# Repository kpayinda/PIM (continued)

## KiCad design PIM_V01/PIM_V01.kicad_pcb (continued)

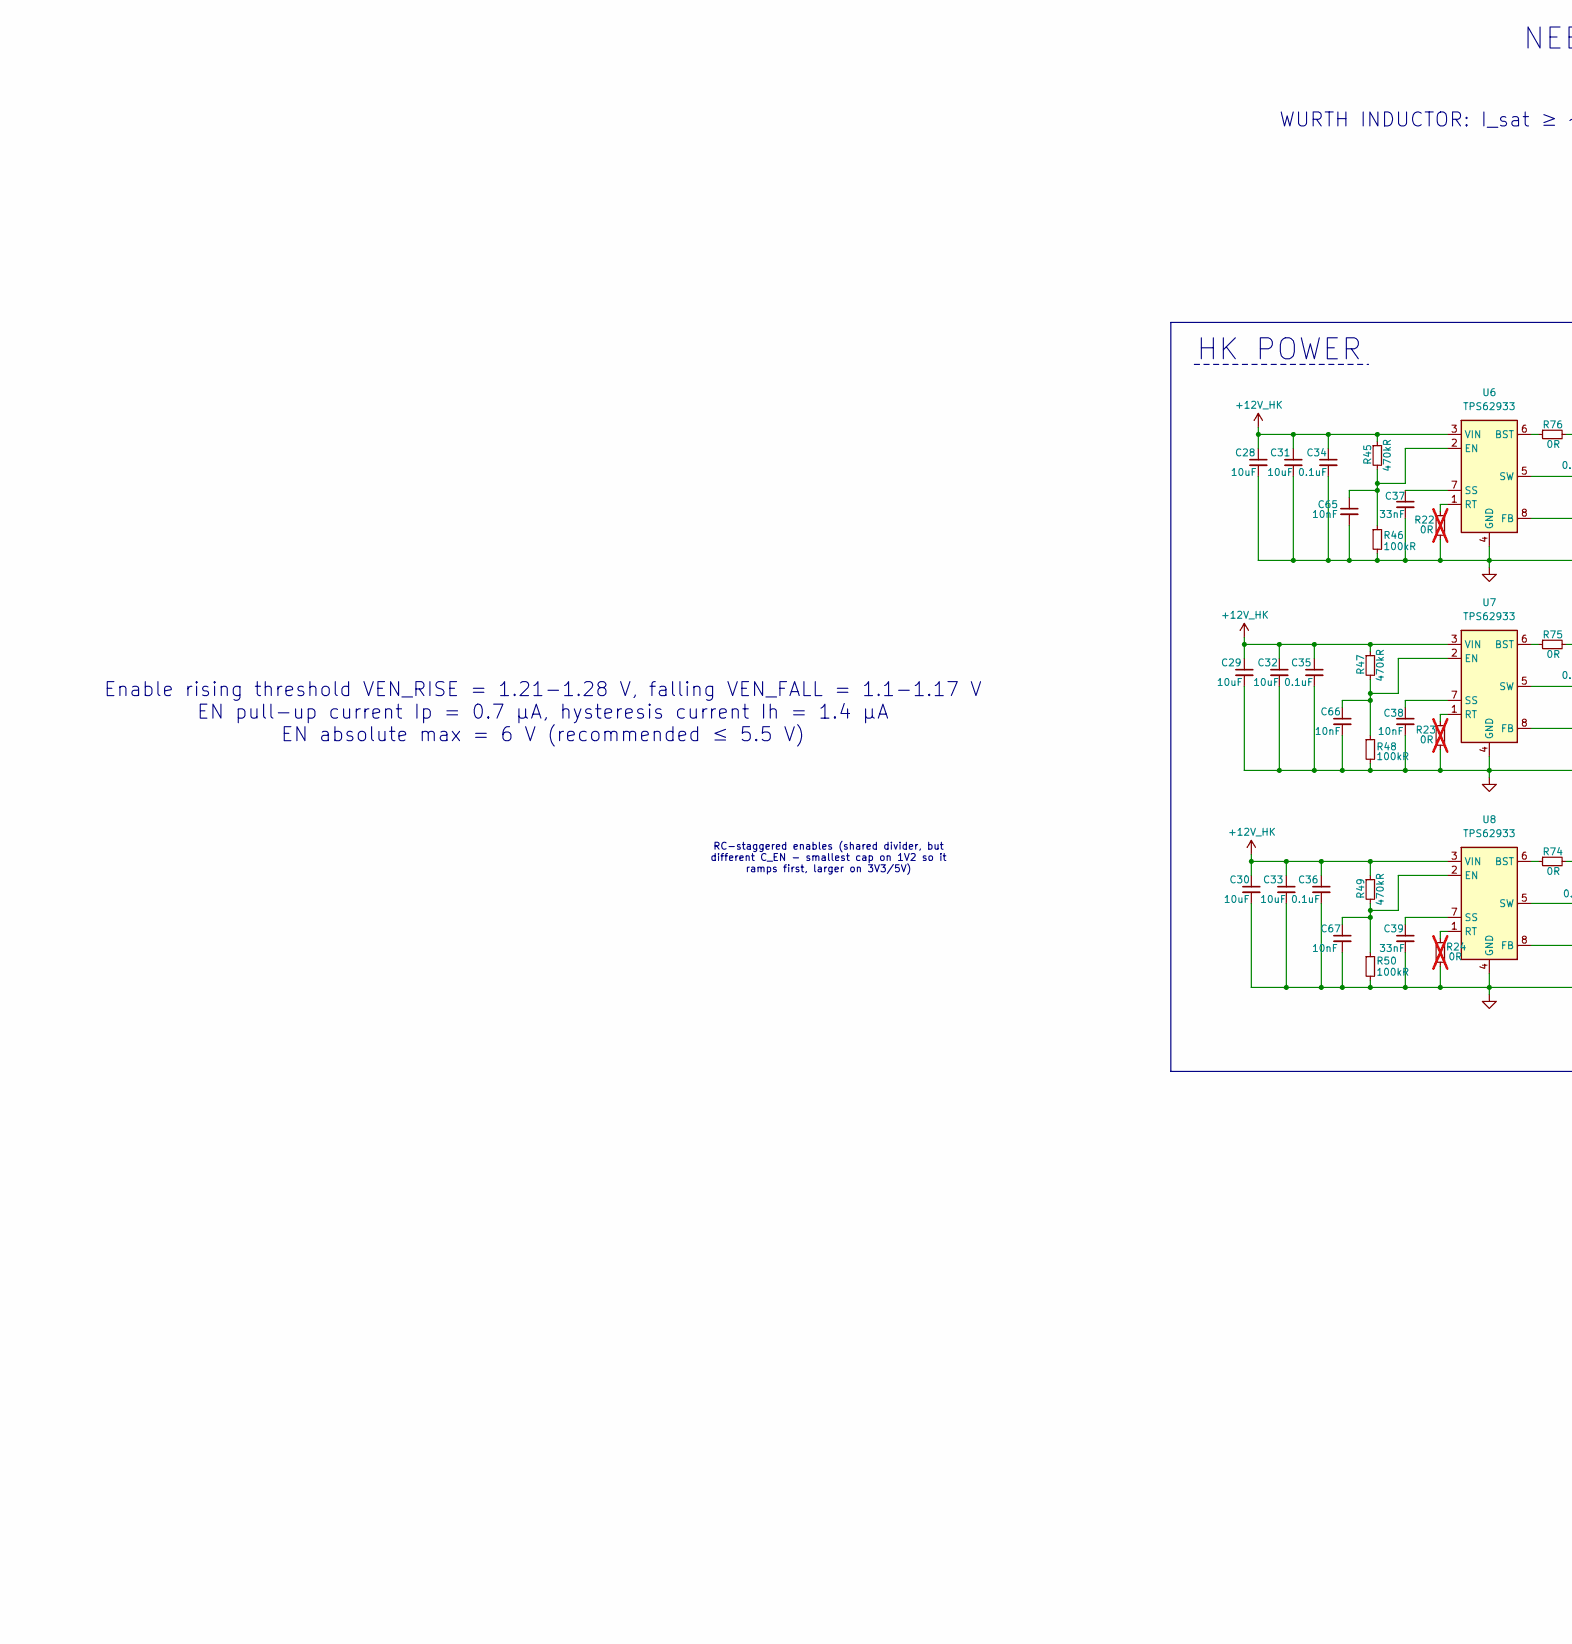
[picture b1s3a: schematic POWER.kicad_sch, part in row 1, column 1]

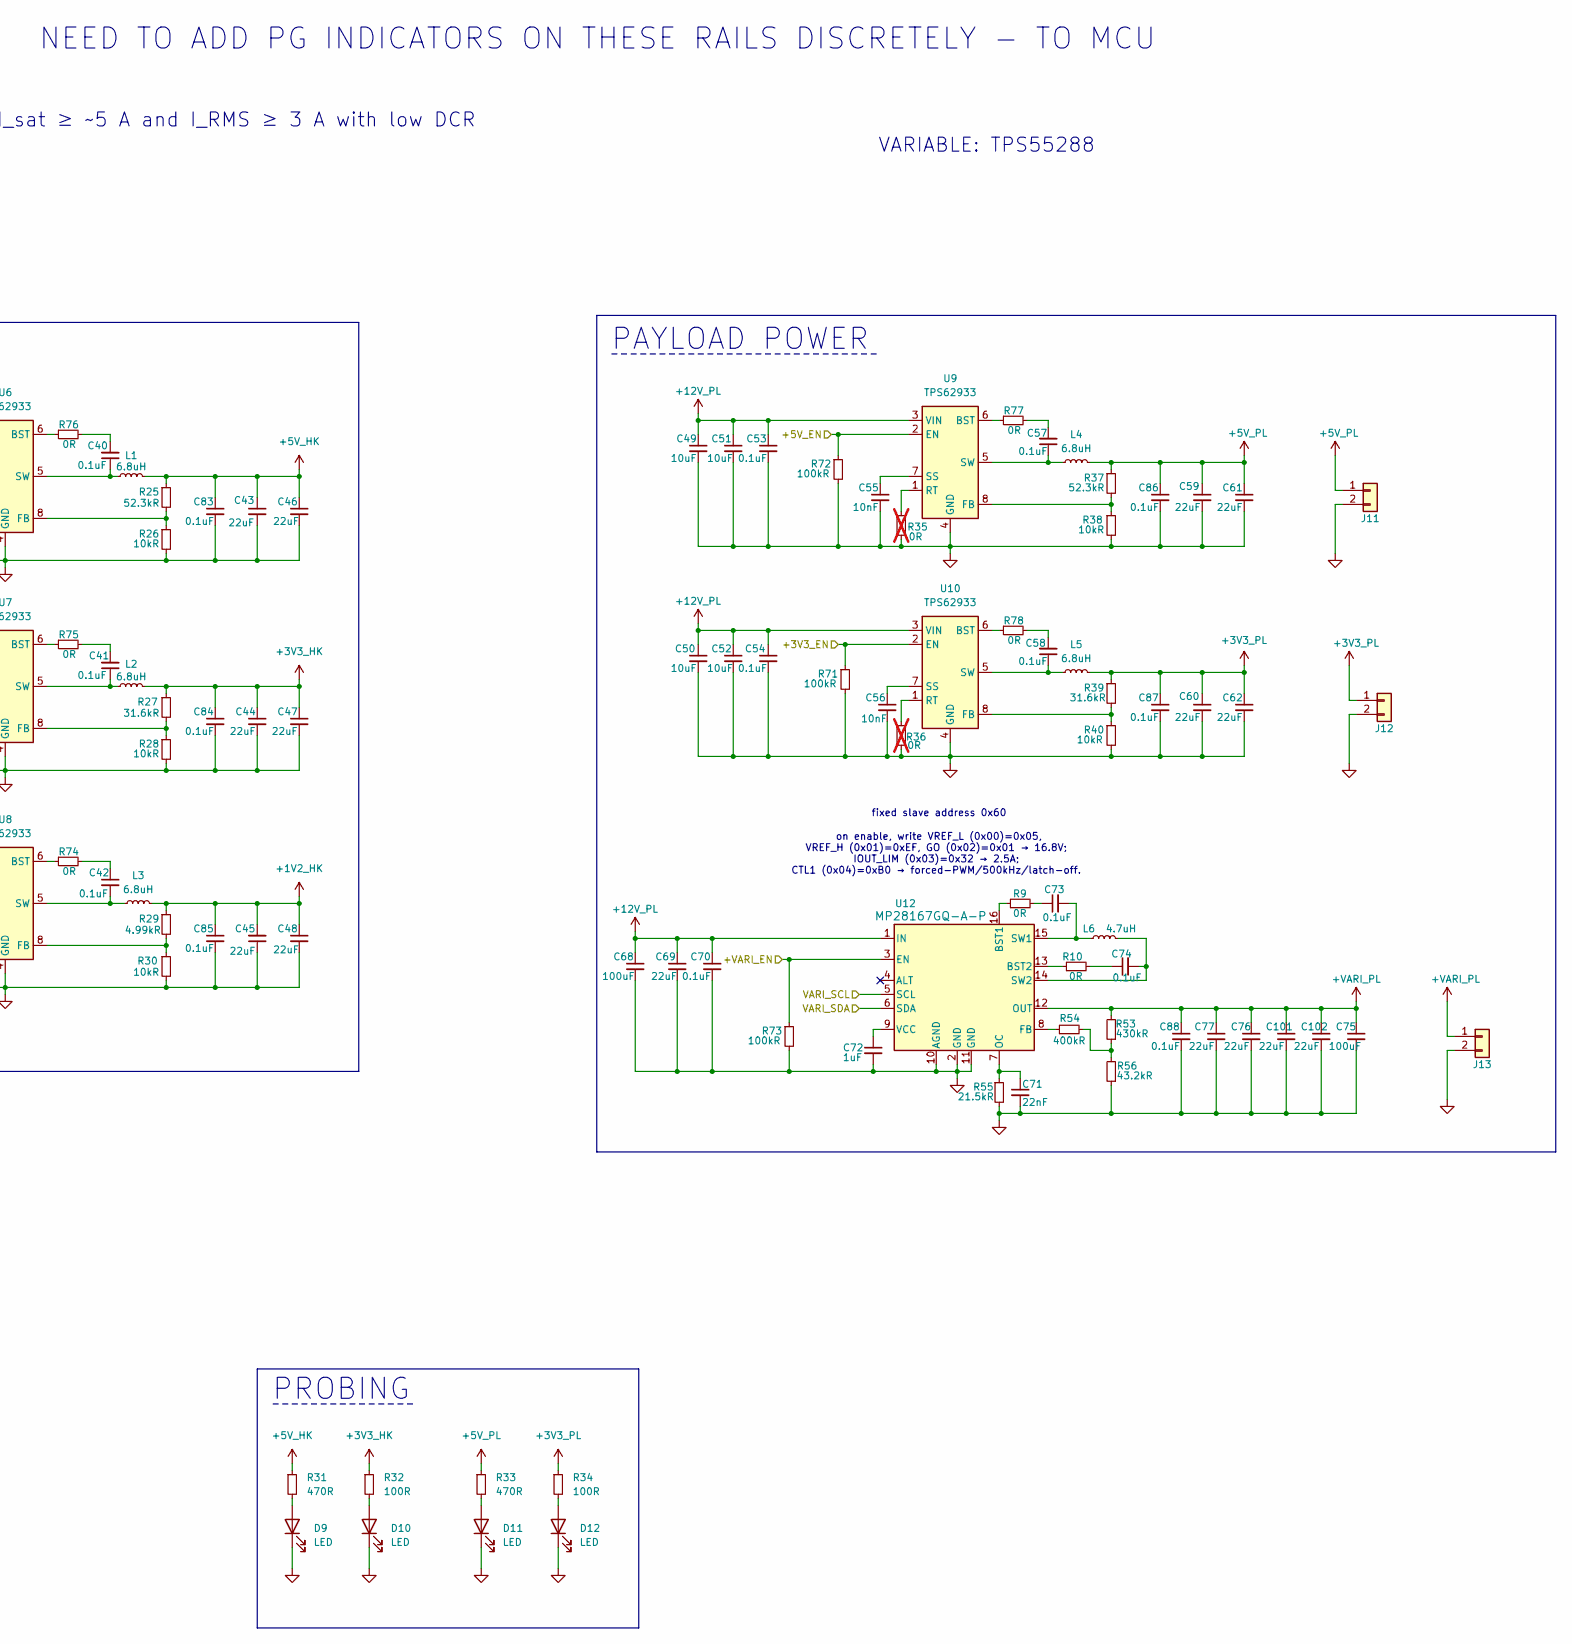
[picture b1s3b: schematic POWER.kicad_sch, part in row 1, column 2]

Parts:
C28, C29, C30, C31, C32, C33, C49, C50, C51, C52: 10uF; C_0603_1608Metric
C34, C35, C36, C40, C41, C42, C53, C54, C57, C58, C70, C73, C74, C83, C84, C85, C86, C87, C88: 0.1uF; C_0603_1608Metric
C37, C39: 33nF; C_0603_1608Metric
C38, C55, C56, C65, C66, C67: 10nF; C_0603_1608Metric
C43, C44, C45, C46, C47, C48, C59, C60, C61, C62, C69, C76, C77, C101, C102: 22uF; C_0603_1608Metric
C68, C75: 100uF; C_0603_1608Metric
C71: 22nF; C_0603_1608Metric
C72: 1uF; C_0603_1608Metric
D9, D10, D11, D12: LED; LED_0603_1608Metric; MPN XL-1608PGC-06
J11, J12, J13: Conn_01x02; PinHeader_1x02_P2.54mm_Vertical
L1, L2, L3, L4, L5: 6.8uH; L_Wurth_WE-LHMI-7030; MPN 74437346068
L6: 4.7uH; L_Wurth_WE-LHMI-7050; MPN 74437349047
R9, R10, R74, R75, R76, R77, R78: 0R; R_0603_1608Metric
R22, R23, R24, R35, R36: 0R; R_0603_1608Metric; not fitted
R25, R37: 52.3kR; R_0603_1608Metric
R26, R28, R30, R38, R40: 10kR; R_0603_1608Metric
R27, R39: 31.6kR; R_0603_1608Metric
R29: 4.99kR; R_0603_1608Metric
R31, R33: 470R; R_0603_1608Metric
R32, R34: 100R; R_0603_1608Metric
R45, R47, R49: 470kR; R_0603_1608Metric
R46, R48, R50, R71, R72, R73: 100kR; R_0603_1608Metric
R53: 430kR; R_0603_1608Metric
R54: 400kR; R_0603_1608Metric
R55: 21.5kR; R_0603_1608Metric
R56: 43.2kR; R_0603_1608Metric
U6, U7, U8, U9, U10: TPS62933; SOT-583-8
U12: MP28167GQ-A-P; QFN-16_MP28167_MNP; MPN MP28167GQ-A-P

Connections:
+1V2_HK: C45.2, C48.1, C85.1, L3.2, R29.1
+3V3_HK: C44.1, C47.1, C84.1, L2.2, R27.1, R32.1; also elsewhere on the board
+3V3_PL: C60.1, C62.1, C87.1, J12.1, L5.2, R34.1, R39.1
+5V_HK: C43.1, C46.1, C83.1, L1.2, R25.1, R31.1; also elsewhere on the board
+5V_PL: C59.1, C61.1, C86.1, J11.1, L4.2, R33.1, R37.1
+12V_HK: C28.1, C29.1, C30.1, C31.1, C32.1, C33.1, C34.1, C35.1, C36.1, R45.1, R47.1, R49.1, U6.3 (VIN), U7.3 (VIN), U8.3 (VIN); also elsewhere on the board
+12V_PL: C49.1, C50.1, C51.1, C52.1, C53.1, C54.1, C68.1, C69.1, C70.1, U9.3 (VIN), U10.3 (VIN), U12.1 (IN); also elsewhere on the board
+VARI_PL: C75.1, C76.1, C77.1, C88.1, C101.1, C102.1, J13.1, R53.2, U12.12 (OUT)
/+3V3_EN: R71.1, U10.2 (EN); also elsewhere on the board
/+5V_EN: R72.1, U9.2 (EN); also elsewhere on the board
/+VARI_EN: R73.1, U12.3 (EN); also elsewhere on the board
/VARI_SCL: U12.5 (SCL); also elsewhere on the board
/VARI_SDA: U12.6 (SDA); also elsewhere on the board
GND: C28.2, C29.2, C30.2, C31.2, C32.2, C33.2, C34.2, C35.2, C36.2, C37.2, C38.2, C39.2, C43.2, C44.2, C45.1, C46.2, C47.2, C48.2, C49.2, C50.2, C51.2, C52.2, C53.2, C54.2, C55.2, C56.2, C59.2, C60.2, C61.2, C62.2, C65.2, C66.2, C67.2, C68.2, C69.2, C70.2, C71.2, C72.2, C75.2, C76.2, C77.2, C83.2, C84.2, C85.2, C86.2, C87.2, C88.2, C101.2, C102.2, D9.1 (K), D10.1 (K), D11.1 (K), D12.1 (K), J11.2, J12.2, J13.2, R22.2, R23.2, R24.2, R26.2, R28.2, R30.2, R35.2, R36.2, R38.2, R40.2, R46.2, R48.2, R50.2, R55.2, R56.1, R71.2, R72.2, R73.2, U6.4 (GND), U7.4 (GND), U8.4 (GND), U9.4 (GND), U10.4 (GND), U12.2 (GND), U12.10 (AGND), U12.11 (GND); also elsewhere on the board
unnamed: C40.2, R76.2
unnamed: C41.2, R75.2
unnamed: C42.1, R74.2
unnamed: C57.2, R77.2
unnamed: C58.2, R78.2
unnamed: C73.1, R9.2
unnamed: C74.1, R10.2
unnamed: D9.2 (A), R31.2
unnamed: D10.2 (A), R32.2
unnamed: D11.2 (A), R33.2
unnamed: D12.2 (A), R34.2
unnamed: R53.1, R54.2, R56.2
unnamed: R76.1, U6.6 (BST)
unnamed: C65.1, R45.2, R46.1, U6.2 (EN)
unnamed: R25.2, R26.1, U6.8 (FB)
unnamed: R22.1, U6.1 (RT)
unnamed: C37.1, U6.7 (SS)
unnamed: C40.1, L1.1, U6.5 (SW)
unnamed: R75.1, U7.6 (BST)
unnamed: C66.1, R47.2, R48.1, U7.2 (EN)
unnamed: R27.2, R28.1, U7.8 (FB)
unnamed: R23.1, U7.1 (RT)
unnamed: C38.1, U7.7 (SS)
unnamed: C41.1, L2.1, U7.5 (SW)
unnamed: R74.1, U8.6 (BST)
unnamed: C67.1, R49.2, R50.1, U8.2 (EN)
unnamed: R29.2, R30.1, U8.8 (FB)
unnamed: R24.1, U8.1 (RT)
unnamed: C39.1, U8.7 (SS)
unnamed: C42.2, L3.1, U8.5 (SW)
unnamed: R77.1, U9.6 (BST)
unnamed: R37.2, R38.1, U9.8 (FB)
unnamed: R35.1, U9.1 (RT)
unnamed: C55.1, U9.7 (SS)
unnamed: C57.1, L4.1, U9.5 (SW)
unnamed: R78.1, U10.6 (BST)
unnamed: R39.2, R40.1, U10.8 (FB)
unnamed: R36.1, U10.1 (RT)
unnamed: C56.1, U10.7 (SS)
unnamed: C58.1, L5.1, U10.5 (SW)
unnamed: R9.1, U12.16 (BST1)
unnamed: R10.1, U12.13 (BST2)
unnamed: R54.1, U12.8 (FB)
unnamed: C71.1, R55.1, U12.7 (OC)
unnamed: C73.2, L6.1, U12.15 (SW1)
unnamed: C74.2, L6.2, U12.14 (SW2)
unnamed: C72.1, U12.9 (VCC)

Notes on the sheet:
PROBING
HK POWER
fixed slave address 0x60
Enable rising threshold VEN_RISE = 1.21-1.28 V, falling VEN_FALL = 1.1-1.17 V EN pull-up current Ip = 0.7 µA, hysteresis current Ih = 1.4 µA EN absolute max = 6 V (recommended ≤ 5.5 V)
WURTH INDUCTOR: I_sat ≥ ~5 A and I_RMS ≥ 3 A with low DCR
VARIABLE: TPS55288
NEED TO ADD PG INDICATORS ON THESE RAILS DISCRETELY - TO MCU
PAYLOAD POWER
on enable, write VREF_L (0x00)=0x05, VREF_H (0x01)=0xEF, GO (0x02)=0x01 → 16.8V; IOUT_LIM (0x03)=0x32 → 2.5A; CTL1 (0x04)=0xB0 → forced-PWM/500kHz/latch-off.
RC-staggered enables (shared divider, but different C_EN - smallest cap on 1V2 so it ramps first, larger on 3V3/5V)

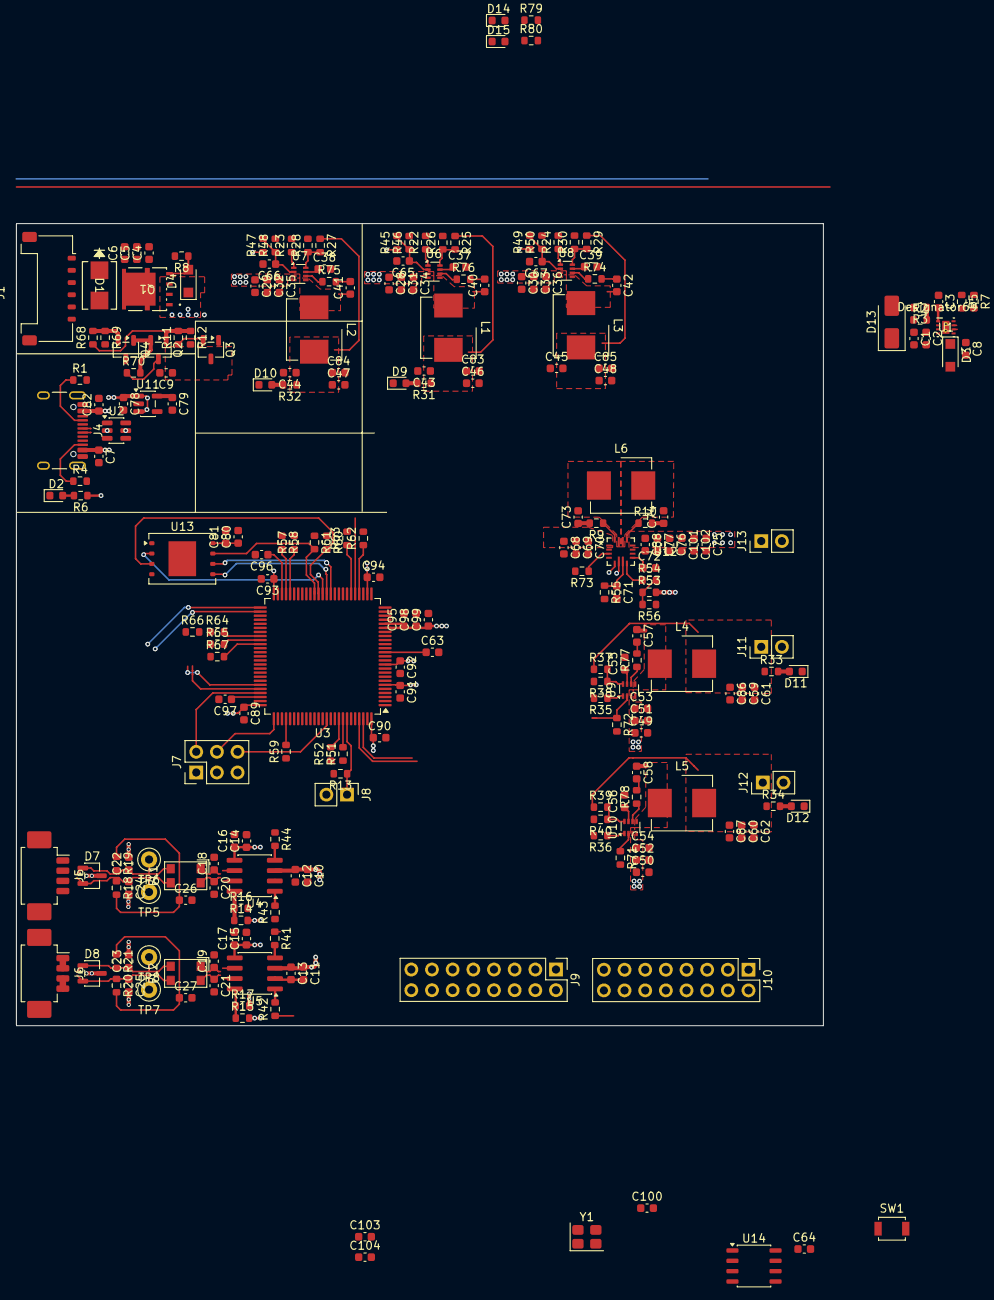
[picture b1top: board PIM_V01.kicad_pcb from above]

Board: 4 copper layers, 99.2 x 98.6 mm, 240 parts (0 on the bottom side), 141 nets.

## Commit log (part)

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2026-06-17 Initial commit of local KiCad project copy
